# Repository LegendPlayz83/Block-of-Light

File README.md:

# Block-of-Light

This is an IRL Minecraft lantern which was created in KiCad 9.0 and Fusion 360. 

<h3>Schematic</h3>

<h3>PCB</h3>

<h3>PCB in 3d</h3>

<h3>Case in 3d</h3>

Credits to: Anay, Rudransh, Ansh, and Nathan

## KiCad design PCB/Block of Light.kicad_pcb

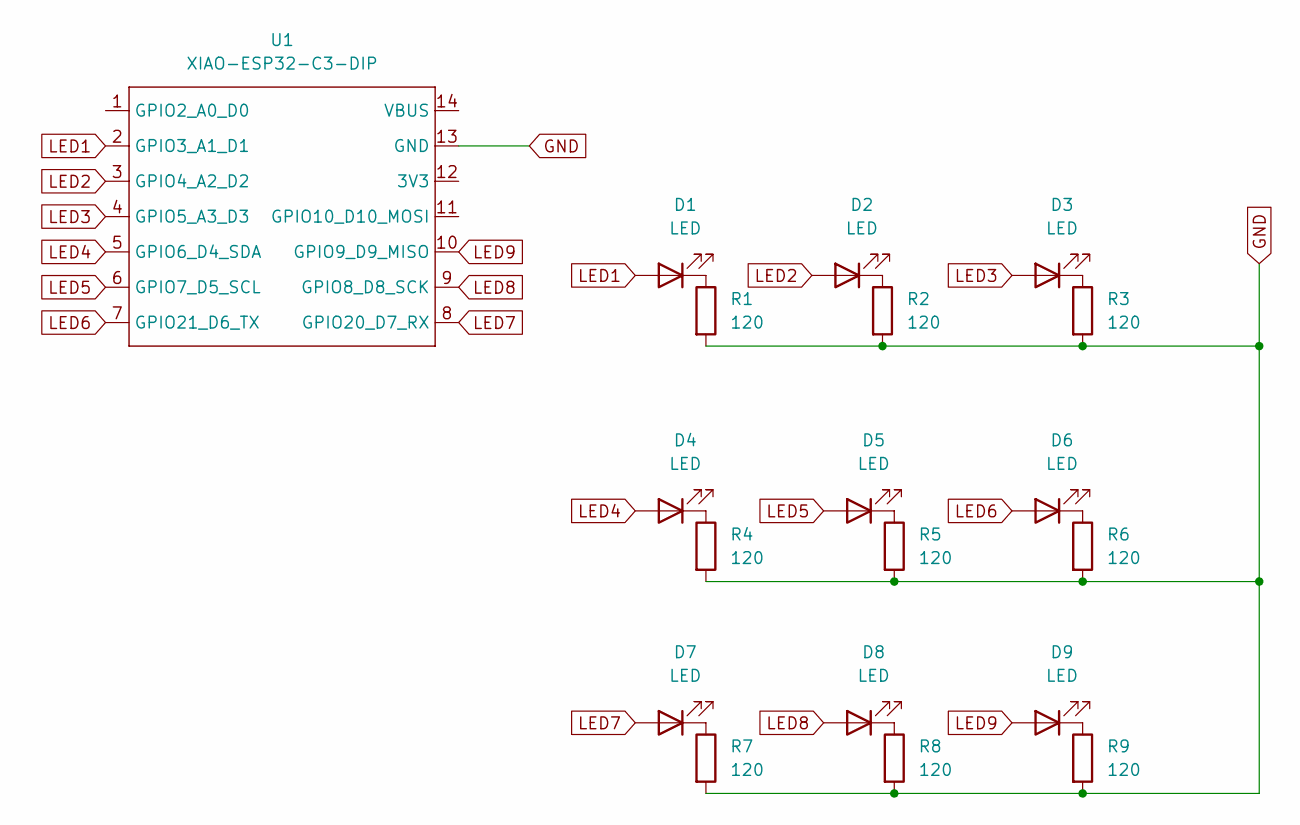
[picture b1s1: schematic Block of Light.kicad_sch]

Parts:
D1, D2, D3, D4, D5, D6, D7, D8, D9: LED; LED_D5.0mm
R1, R2, R3, R4, R5, R6, R7, R8, R9: 120; R_Axial_DIN0207_L6.3mm_D2.5mm_P7.62mm_Horizontal
U1: XIAO-ESP32-C3-DIP

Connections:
GND: R1.2, R2.2, R3.2, R4.2, R5.2, R6.2, R7.2, R8.2, R9.2, U1.13 (GND)
LED1: D1.2 (A), U1.2 (GPIO3_A1_D1)
LED2: D2.2 (A), U1.3 (GPIO4_A2_D2)
LED3: D3.2 (A), U1.4 (GPIO5_A3_D3)
LED4: D4.2 (A), U1.5 (GPIO6_D4_SDA)
LED5: D5.2 (A), U1.6 (GPIO7_D5_SCL)
LED6: D6.2 (A), U1.7 (GPIO21_D6_TX)
LED7: D7.2 (A), U1.8 (GPIO20_D7_RX)
LED8: D8.2 (A), U1.9 (GPIO8_D8_SCK)
LED9: D9.2 (A), U1.10 (GPIO9_D9_MISO)
unnamed: D1.1 (K), R1.1
unnamed: D2.1 (K), R2.1
unnamed: D3.1 (K), R3.1
unnamed: D4.1 (K), R4.1
unnamed: D5.1 (K), R5.1
unnamed: D6.1 (K), R6.1
unnamed: D7.1 (K), R7.1
unnamed: D8.1 (K), R8.1
unnamed: D9.1 (K), R9.1

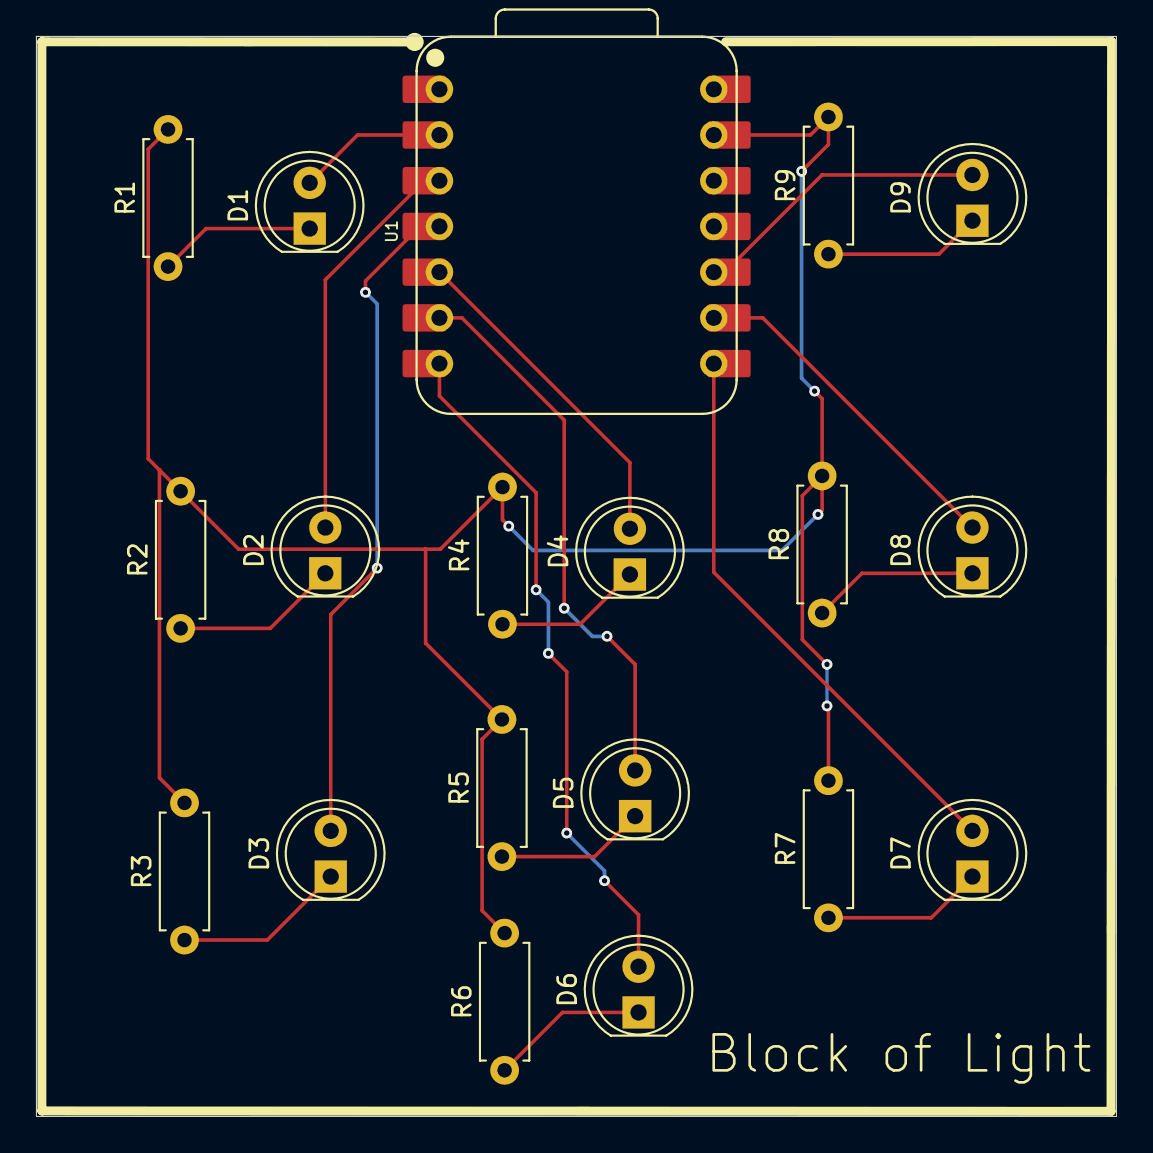
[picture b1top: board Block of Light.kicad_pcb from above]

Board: 2 copper layers, 60.0 x 60.0 mm, 19 parts (0 on the bottom side), 19 nets.

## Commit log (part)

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2026-03-15 Update README with project description
    Added a brief description of the Block-of-Light project.
2026-03-15 Update README with images and additional sections
    Added images and sections for schematic, PCB, and case in 3D.
